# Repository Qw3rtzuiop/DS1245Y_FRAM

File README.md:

# DS1245Y drop in replacement with FM28V100 FRAM

Take a look here: @braddr discovered an easier solution:
https://github.com/Qw3rtzuiop/DS1245Y_FRAM/issues/1#issuecomment-2248997533

Designed for Keithley 2001 (MEM2 option). More infos here:
https://xdevs.com/article/kei200x-mem/

Idea from TxB @eevblog forum: https://www.eevblog.com/forum/testgear/tek-csa7404-repair-project/msg1404582/#msg1404582

Now tested and working.

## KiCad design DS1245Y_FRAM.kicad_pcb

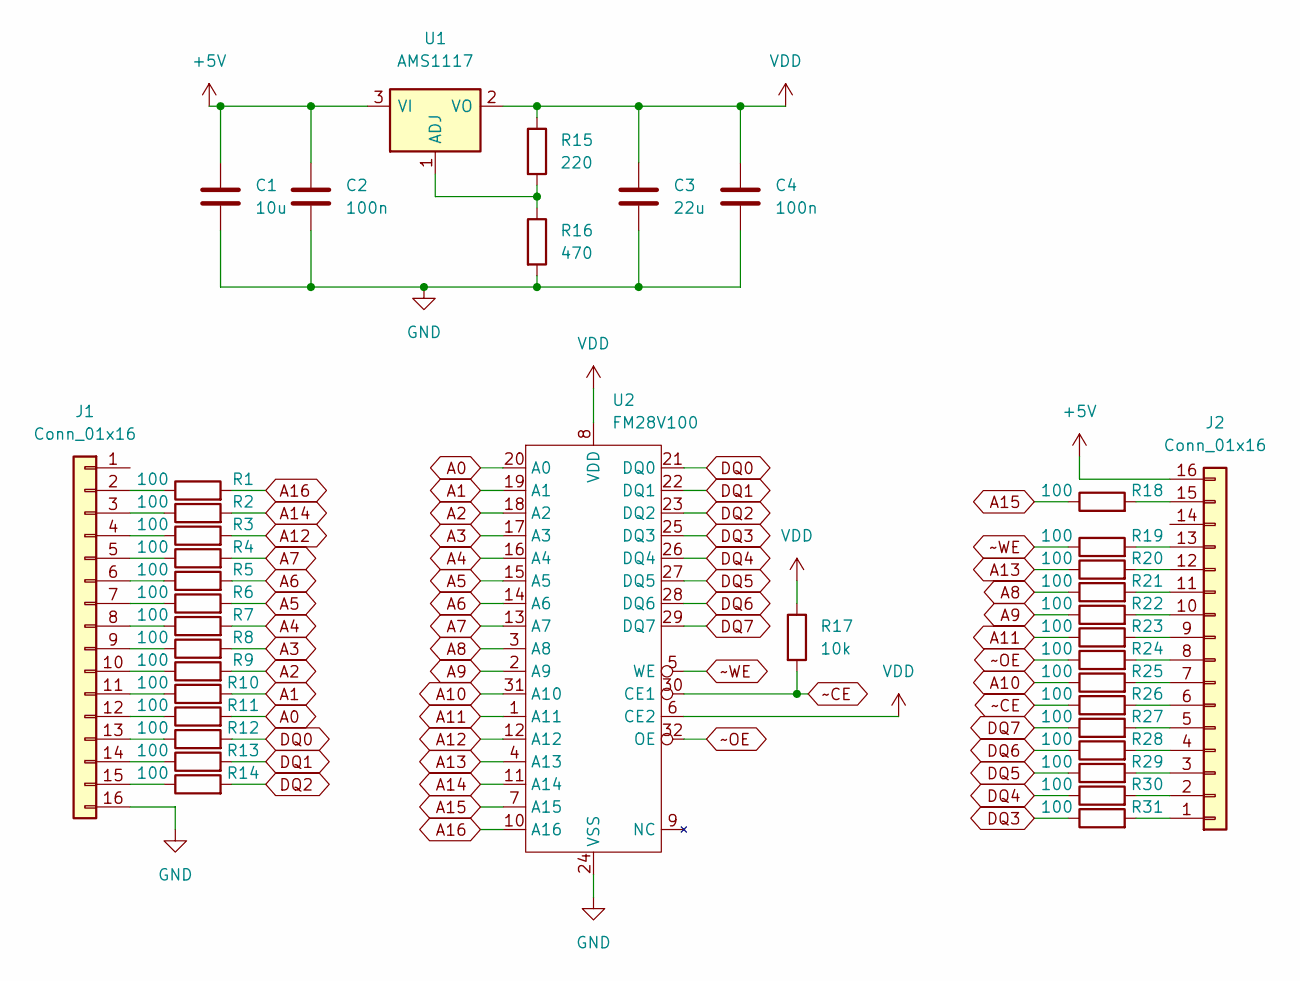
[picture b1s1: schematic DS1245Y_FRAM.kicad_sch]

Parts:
C1: 10u; C_0805_2012Metric
C2, C4: 100n; C_0805_2012Metric
C3: 22u; C_0805_2012Metric
J1, J2: Conn_01x16; PinHeader_1x16_P2.54mm_Vertical
R1, R2, R3, R4, R5, R6, R7, R8, R9, R10, R11, R12, R13, R14, R18, R19, R20, R21, R22, R23, R24, R25, R26, R27, R28, R29, R30, R31: 100; R_0805_2012Metric
R15: 220; R_0805_2012Metric
R16: 470; R_0805_2012Metric
R17: 10k; R_0805_2012Metric
U1: AMS1117; SOT-223-3_TabPin2
U2: FM28V100; TSOP-I-32_11.8x8mm_P0.5mm

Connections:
+5V: C1.1, C2.1, J2.16, U1.3 (VI)
A0: R11.2, U2.20 (A0)
A1: R10.2, U2.19 (A1)
A2: R9.2, U2.18 (A2)
A3: R8.2, U2.17 (A3)
A4: R7.2, U2.16 (A4)
A5: R6.2, U2.15 (A5)
A6: R5.2, U2.14 (A6)
A7: R4.2, U2.13 (A7)
A8: R21.1, U2.3 (A8)
A9: R22.1, U2.2 (A9)
A10: R25.1, U2.31 (A10)
A11: R23.1, U2.1 (A11)
A12: R3.2, U2.12 (A12)
A13: R20.1, U2.4 (A13)
A14: R2.2, U2.11 (A14)
A15: R18.1, U2.7 (A15)
A16: R1.2, U2.10 (A16)
DQ0: R12.2, U2.21 (DQ0)
DQ1: R13.2, U2.22 (DQ1)
DQ2: R14.2, U2.23 (DQ2)
DQ3: R31.1, U2.25 (DQ3)
DQ4: R30.1, U2.26 (DQ4)
DQ5: R29.1, U2.27 (DQ5)
DQ6: R28.1, U2.28 (DQ6)
DQ7: R27.1, U2.29 (DQ7)
GND: C1.2, C2.2, C3.2, C4.2, J1.16, R16.2, U2.24 (VSS)
unnamed: J1.2, R1.1
unnamed: J1.3, R2.1
unnamed: J1.4, R3.1
unnamed: J1.5, R4.1
unnamed: J1.6, R5.1
unnamed: J1.7, R6.1
unnamed: J1.8, R7.1
unnamed: J1.9, R8.1
unnamed: J1.10, R9.1
unnamed: J1.11, R10.1
unnamed: J1.12, R11.1
unnamed: J1.13, R12.1
unnamed: J1.14, R13.1
unnamed: J1.15, R14.1
unnamed: J2.1, R31.2
unnamed: J2.2, R30.2
unnamed: J2.3, R29.2
unnamed: J2.4, R28.2
unnamed: J2.5, R27.2
unnamed: J2.6, R26.2
unnamed: J2.7, R25.2
unnamed: J2.8, R24.2
unnamed: J2.9, R23.2
unnamed: J2.10, R22.2
unnamed: J2.11, R21.2
unnamed: J2.12, R20.2
unnamed: J2.13, R19.2
unnamed: J2.15, R18.2
unnamed: R15.2, R16.1, U1.1 (ADJ)
VDD: C3.1, C4.1, R15.1, R17.1, U1.2 (VO), U2.6 (CE2), U2.8 (VDD)
~CE: R17.2, R26.1, U2.30 (CE1)
~OE: R24.1, U2.32 (OE)
~WE: R19.1, U2.5 (WE)

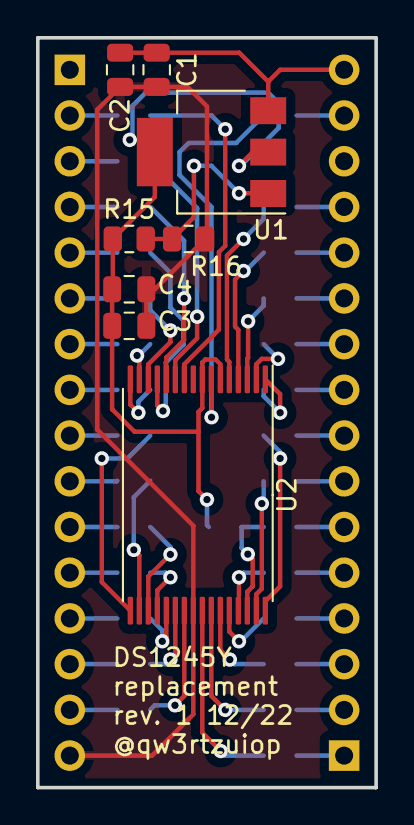
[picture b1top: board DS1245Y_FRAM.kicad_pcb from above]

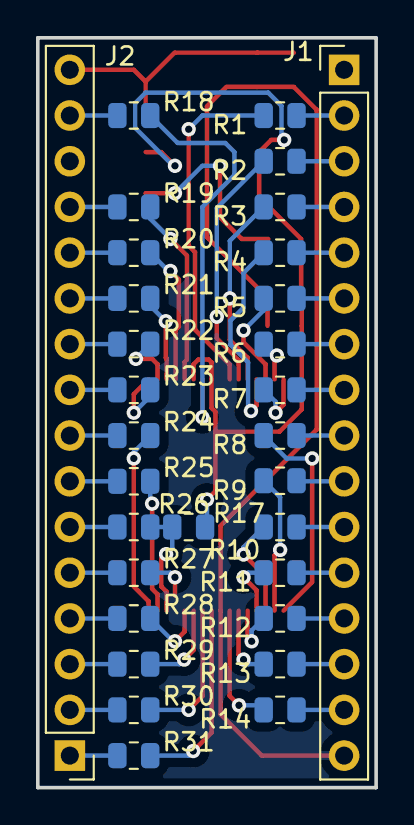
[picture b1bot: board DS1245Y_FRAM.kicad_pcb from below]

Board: 2 copper layers, 18.8 x 41.7 mm, 39 parts (31 on the bottom side), 60 nets.

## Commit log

2022-12-17 kicad.gitignore aktualisiert
2022-12-17 rev. 0
2022-12-29 rev. 1
